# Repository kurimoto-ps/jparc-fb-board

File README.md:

# J-PARC MR 主電磁石電源フィードバック制御子基板

J-PARC メインリング（MR）の主電磁石電源で、電流パタンに沿って電磁石電流を制御するための子基板です。既設のフィードバック母基板 **TEP521C** を使い、その上の **HUMANDATA ACM-205** を、STM32H745 と MAX 10 を搭載した本基板に置き換えます。

既設の光受信、D/A 出力、PLC、変換器盤への Duty 指令は母基板のコネクタを通ります。新たに Ethernet と SDRAM を子基板に持たせ、これまで独立したパタンメモリ基板が担っていた電流指令の受信・保持を取り込むことが設計の狙いです。

光 ADC の混在構成では、MAX 10 が **24 bit × 3 系統**と **16 bit × 8 ch（ADS8568）**を受信します。ACM-205 を置き換えた試作機では、STM32 の起動、SDRAM、Ethernet、FPGA との通信に加え、16 bit 側の全 8 ch のノコギリ波と、24 bit 側の DCCT P/N の一定入力を、それぞれ対応する DAC 出力で確認しました。[ADC の信号経路](docs/interfaces.md) · [実機試験の結果](verification/bench-tests.md)

現行基板では J4 の書き込みケーブルと J5 の RJ45 ジャックに個別の対処を行っています。[既知不具合 3 件と次回改版](docs/errata.md)

```mermaid
flowchart TD
    Host["パタン作成システム"] -->|Ethernet| MCU
    subgraph Board["本基板"]
        MCU["STM32H745"] <-->|FMC 16 bit| RAM["SDRAM 8 MiB"]
        MCU <-->|SPI 4系統| FPGA["MAX 10"]
    end
    Mother["既設フィードバック母基板 TEP521C"]
    MCU <-->|PLC用GPIOなど| Mother
    Mother -->|受信データ・外部同期| FPGA
    FPGA -->|DAC制御・Duty指令など| Mother
    OE["6ch O/E基板"] -->|帰還信号| Mother
    Mother -->|ADS8568 のクロック・変換制御| EO["E/O基板 TEP526A"]
    Mother --> DAC["16ch D/A基板"]
    Mother --> Power["変換器盤への指令"]
```

## 設計を読む

| 知りたいこと | 資料 |
| --- | --- |
| 回路全体と部品の接続 | [回路図 PDF 全6ページ](docs/drawings/schematic.pdf) |
| 基板の配線と両面の部品配置 | [配線・配置図 PDF 全10ページ](docs/drawings/pcb-patterns.pdf) |
| 回路図・PCB の編集 | [KiCad プロジェクト](hardware/kicad/JPARC_PS_FB_BOARD.kicad_pro) |
| プロセッサの役割、電源、メモリ、クロック | [ハードウェア構成](docs/hardware.md) |
| 母基板との対応、ADC/DAC の接点と FPGA ボール | [外部インターフェース](docs/interfaces.md) |
| ランド単位のネット名、部品座標 | [ピン・ネット対応 CSV](hardware/tables/pin-net-mapping.csv) · [部品配置 CSV](hardware/tables/component-locations.csv) |
| 基板製造・部品実装に実際に渡したデータ | [PCBWay の裸基板 Gerber・ドリル、P板.com の実装指示書・部品表・マウントデータ・ステンシル](manufacturing/README.md) |
| 接続・DRC の検査結果と原本の識別 | [設計検証記録](verification/README.md) |

このリポジトリの対象は子基板のハードウェアです。MCU の制御ソフトウェア、MAX 10 の動作用 HDL、閉ループでの追従性能・遅延・ジッタの実測値は収録していません。図は設計上の信号経路を示します。

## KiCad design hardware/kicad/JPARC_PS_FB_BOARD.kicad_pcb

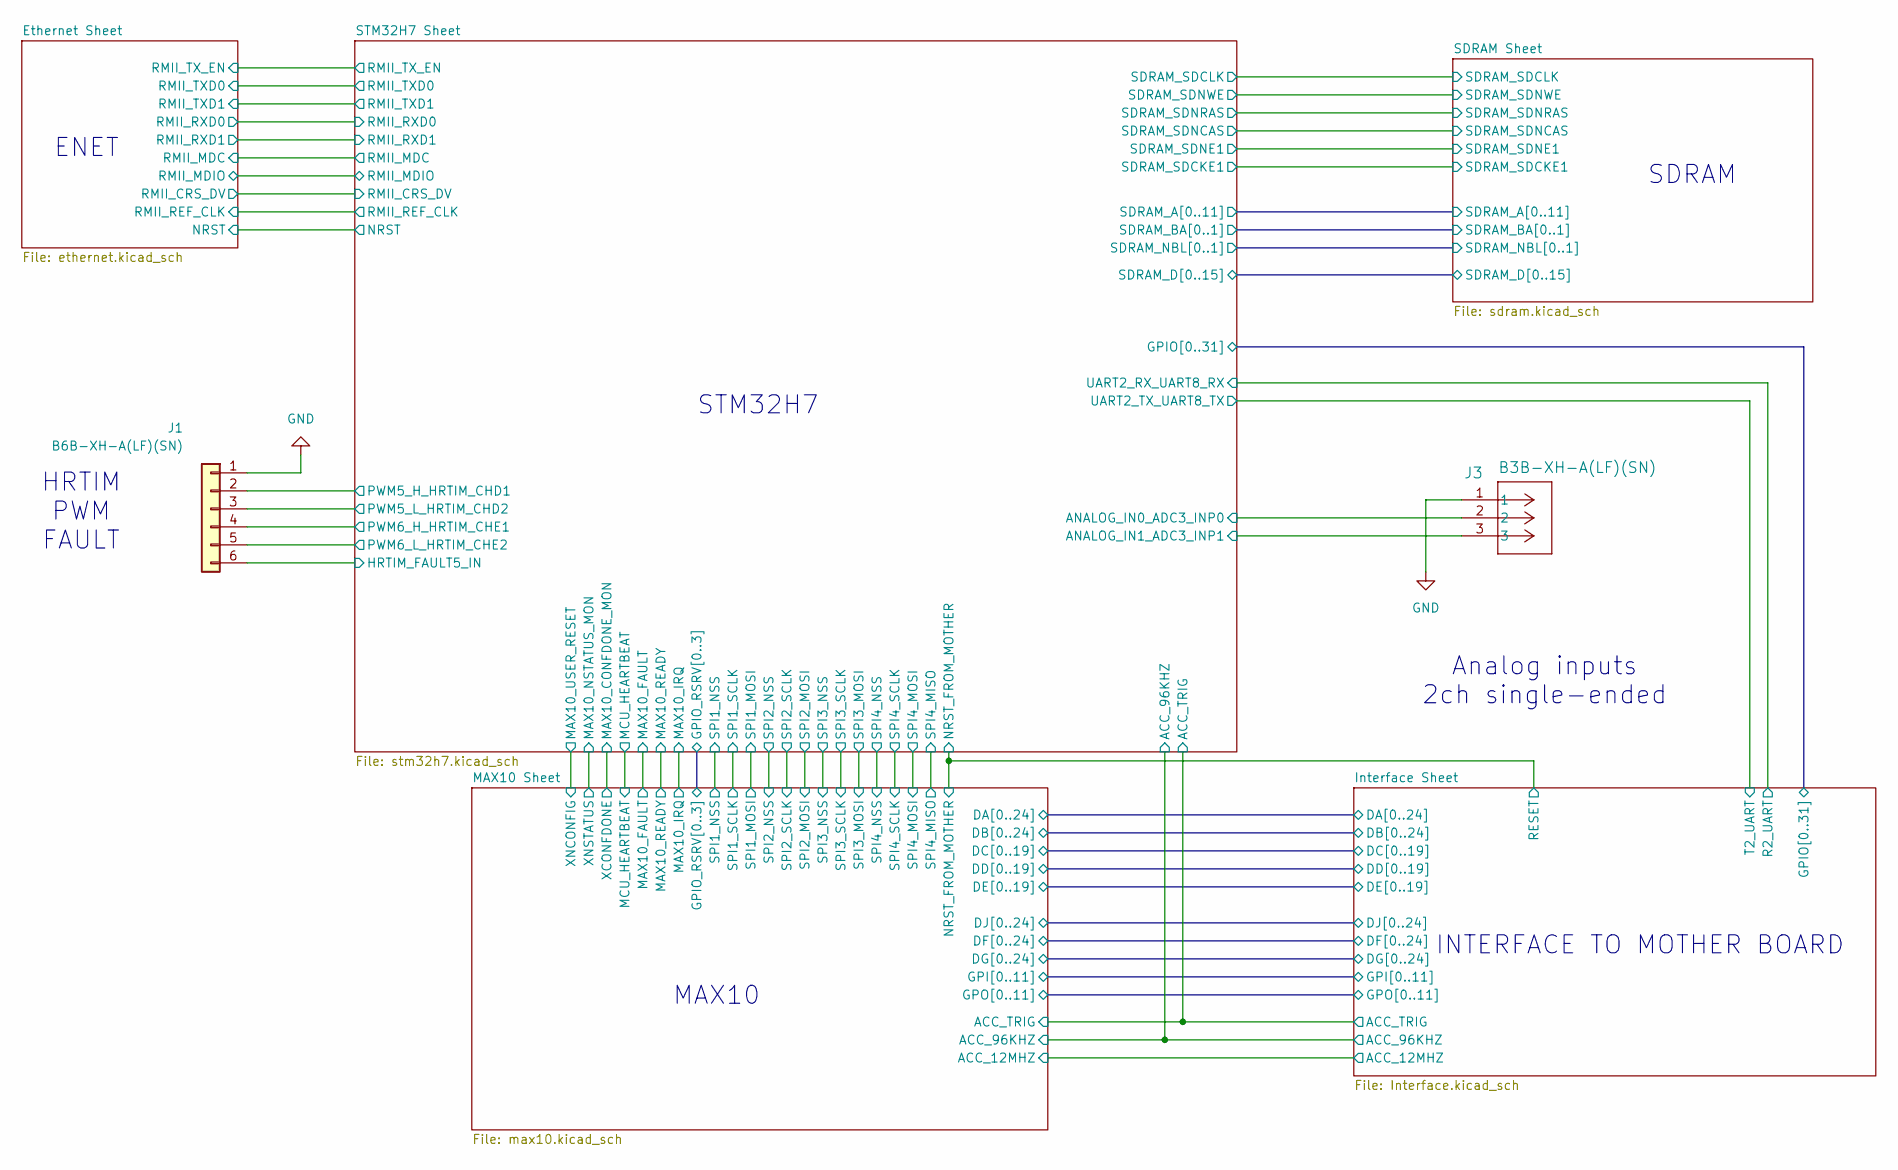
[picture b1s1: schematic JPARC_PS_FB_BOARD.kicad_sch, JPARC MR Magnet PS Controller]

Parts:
J1: B6B-XH-A(LF)(SN); JST_XH_B6B-XH-A_1x06_P2.50mm_Vertical
J3: B3B-XH-A(LF)(SN); JST_XH_B3B-XH-A_1x03_P2.50mm_Vertical

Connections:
/STM32H7 Sheet/PA11: J1.2; also elsewhere on the board
/STM32H7 Sheet/PA12: J1.3; also elsewhere on the board
/STM32H7 Sheet/PC2_C: J3.2; also elsewhere on the board
/STM32H7 Sheet/PC3_C: J3.3; also elsewhere on the board
/STM32H7 Sheet/PG6: J1.4; also elsewhere on the board
/STM32H7 Sheet/PG7: J1.5; also elsewhere on the board
/STM32H7 Sheet/PG10: J1.6; also elsewhere on the board
GND: J1.1, J3.1; also elsewhere on the board

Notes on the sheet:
SDRAM
INTERFACE TO MOTHER BOARD
HRTIM PWM FAULT
Analog inputs 2ch single-ended
MAX10
STM32H7
ENET

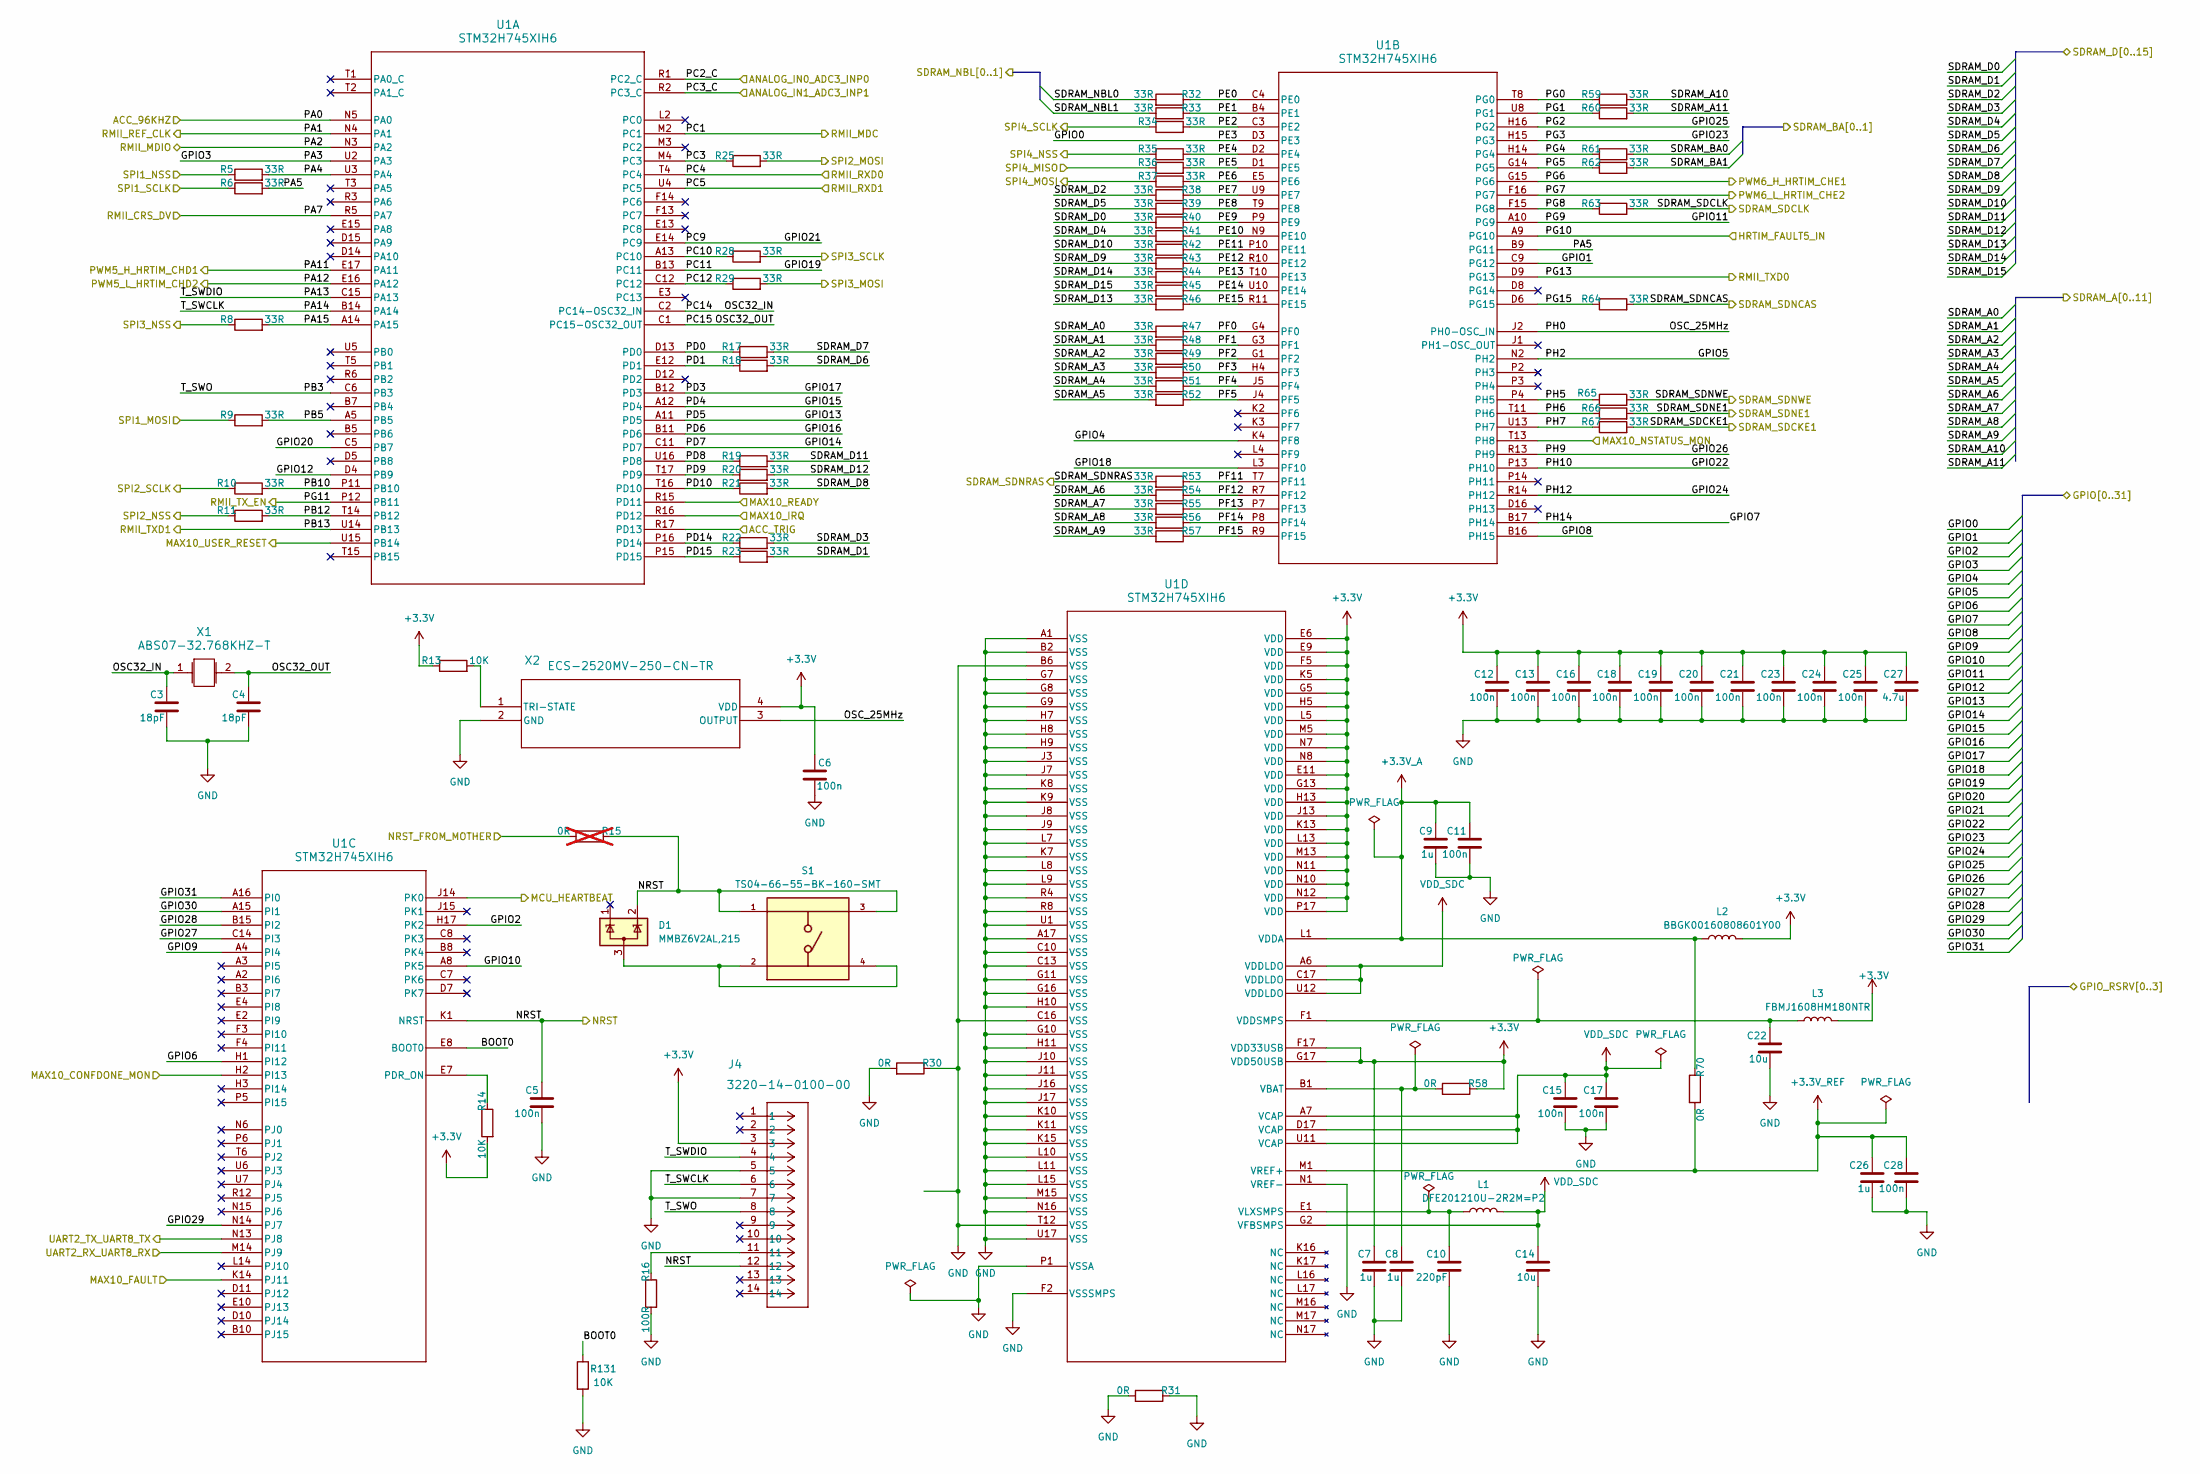
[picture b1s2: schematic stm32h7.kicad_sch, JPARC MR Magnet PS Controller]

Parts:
C3, C4: 18pF; C_0603_1608Metric
C5, C6, C11, C12, C13, C15, C16, C17, C18, C19, C20, C21, C23, C24, C25, C28: 100n; C_0402_1005Metric
C7, C8: 1u; C_0402_1005Metric
C9, C26: 1u; C_0603_1608Metric
C10: 220pF; C_0402_1005Metric
C14, C22: 10u; C_0603_1608Metric
C27: 4.7u; C_0805_2012Metric
D1: MMBZ6V2AL,215; SOT-23-3
J4: 3220-14-0100-00; CNCtech_3220_14_0100_00_Checked
L1: DFE201210U-2R2M=P2; L_Murata_DFE201210U
L2: BBGK00160808601Y00; L_0603_1608Metric
L3: FBMJ1608HM180NTR; L_0603_1608Metric
R5, R6, R8, R9, R10, R11, R17, R18, R19, R20, R21, R22, R23, R25, R28, R29, R32, R33, R34, R35, R36, R37, R38, R39, R40, R41, R42, R43, R44, R45, R46, R47, R48, R49, R50, R51, R52, R53, R54, R55, R56, R57, R59, R60, R61, R62, R63, R64, R65, R66, R67: 33R; R_0402_1005Metric
R13, R14, R131: 10K; R_0603_1608Metric
R15: 0R; R_0603_1608Metric; not fitted
R16: 100R; R_0603_1608Metric
R30, R31, R58, R70: 0R; R_0603_1608Metric
S1: TS04-66-55-BK-160-SMT; SW_TS04-66-55-BK-160-SMT; PARTREV 1.0
U1: STM32H745XIH6; TFBGA240&plus_25
X1: ABS07-32.768KHZ-T; CAP_ABS07-32.768KHZ-T_ABR
X2: ECS-2520MV-250-CN-TR; OSC_ECS-2520MV_ECS

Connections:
+3.3V: C6.1, C7.1, C12.1, C13.1, C16.1, C18.1, C19.1, C20.1, C21.1, C23.1, C24.1, C25.1, C27.1, J4.3, L2.2, L3.1, R13.1, R14.2, R58.1, U1.E6 (VDD), U1.E9 (VDD), U1.E11 (VDD), U1.F5 (VDD), U1.F17 (VDD33USB), U1.G5 (VDD), U1.G13 (VDD), U1.G17 (VDD50USB), U1.H5 (VDD), U1.H13 (VDD), U1.J13 (VDD), U1.K5 (VDD), U1.K13 (VDD), U1.L5 (VDD), U1.L13 (VDD), U1.M5 (VDD), U1.M13 (VDD), U1.N7 (VDD), U1.N8 (VDD), U1.N10 (VDD), U1.N11 (VDD), U1.N12 (VDD), U1.P17 (VDD), X2.4 (VDD); also elsewhere on the board
+3.3V_A: C9.1, C11.1, L2.1, R70.1, U1.L1 (VDDA)
+3.3V_REF: C26.1, C28.1, R70.2, U1.M1 (VREF+)
/Interface Sheet/ACC_TRIG: U1.R17 (PD13); also elsewhere on the board
/Interface Sheet/GPIO0: U1.D3 (PE3); also elsewhere on the board
/Interface Sheet/GPIO1: U1.C9 (PG12); also elsewhere on the board
/Interface Sheet/GPIO2: U1.H17 (PK2); also elsewhere on the board
/Interface Sheet/GPIO3: U1.U2 (PA3); also elsewhere on the board
/Interface Sheet/GPIO4: U1.K4 (PF8); also elsewhere on the board
/Interface Sheet/GPIO5: U1.N2 (PH2); also elsewhere on the board
/Interface Sheet/GPIO6: U1.H1 (PI12); also elsewhere on the board
/Interface Sheet/GPIO7: U1.B17 (PH14); also elsewhere on the board
/Interface Sheet/GPIO8: U1.B16 (PH15); also elsewhere on the board
/Interface Sheet/GPIO9: U1.A4 (PI4); also elsewhere on the board
/Interface Sheet/GPIO10: U1.A8 (PK5); also elsewhere on the board
/Interface Sheet/GPIO11: U1.A10 (PG9); also elsewhere on the board
/Interface Sheet/GPIO12: U1.D4 (PB9); also elsewhere on the board
/Interface Sheet/GPIO13: U1.A11 (PD5); also elsewhere on the board
/Interface Sheet/GPIO14: U1.C11 (PD7); also elsewhere on the board
/Interface Sheet/GPIO15: U1.A12 (PD4); also elsewhere on the board
/Interface Sheet/GPIO16: U1.B11 (PD6); also elsewhere on the board
/Interface Sheet/GPIO17: U1.B12 (PD3); also elsewhere on the board
/Interface Sheet/GPIO18: U1.L3 (PF10); also elsewhere on the board
/Interface Sheet/GPIO19: U1.B13 (PC11); also elsewhere on the board
/Interface Sheet/GPIO20: U1.C5 (PB7); also elsewhere on the board
/Interface Sheet/GPIO21: U1.E14 (PC9); also elsewhere on the board
/Interface Sheet/GPIO22: U1.P13 (PH10); also elsewhere on the board
/Interface Sheet/GPIO23: U1.H15 (PG3); also elsewhere on the board
/Interface Sheet/GPIO24: U1.R14 (PH12); also elsewhere on the board
/Interface Sheet/GPIO25: U1.H16 (PG2); also elsewhere on the board
/Interface Sheet/GPIO26: U1.R13 (PH9); also elsewhere on the board
/Interface Sheet/GPIO27: U1.C14 (PI3); also elsewhere on the board
/Interface Sheet/GPIO28: U1.B15 (PI2); also elsewhere on the board
/Interface Sheet/GPIO29: U1.N14 (PJ7); also elsewhere on the board
/Interface Sheet/GPIO30: U1.A15 (PI1); also elsewhere on the board
/Interface Sheet/GPIO31: U1.A16 (PI0); also elsewhere on the board
/Interface Sheet/R2_UART: U1.M14 (PJ9); also elsewhere on the board
/Interface Sheet/RESET: R15.2; also elsewhere on the board
/Interface Sheet/T2_UART: U1.N13 (PJ8); also elsewhere on the board
/MAX10 Sheet/MAX10_FAULT: U1.K14 (PJ11); also elsewhere on the board
/MAX10 Sheet/MAX10_IRQ: U1.R16 (PD12); also elsewhere on the board
/MAX10 Sheet/MAX10_READY: U1.R15 (PD11); also elsewhere on the board
/MAX10 Sheet/MCU_HEARTBEAT: U1.J14 (PK0); also elsewhere on the board
/MAX10 Sheet/SPI1_MOSI: R9.1; also elsewhere on the board
/MAX10 Sheet/SPI1_NSS: R5.1; also elsewhere on the board
/MAX10 Sheet/SPI1_SCLK: R6.1; also elsewhere on the board
/MAX10 Sheet/SPI2_MOSI: R25.2; also elsewhere on the board
/MAX10 Sheet/SPI2_NSS: R11.1; also elsewhere on the board
/MAX10 Sheet/SPI2_SCLK: R10.1; also elsewhere on the board
/MAX10 Sheet/SPI3_MOSI: R29.2; also elsewhere on the board
/MAX10 Sheet/SPI3_NSS: R8.1; also elsewhere on the board
/MAX10 Sheet/SPI3_SCLK: R28.2; also elsewhere on the board
/MAX10 Sheet/SPI4_MISO: R36.1; also elsewhere on the board
/MAX10 Sheet/SPI4_MOSI: R37.1; also elsewhere on the board
/MAX10 Sheet/SPI4_NSS: R35.1; also elsewhere on the board
/MAX10 Sheet/SPI4_SCLK: R34.1; also elsewhere on the board
/MAX10 Sheet/XCONFDONE: U1.H2 (PI13); also elsewhere on the board
/MAX10 Sheet/XNCONFIG: U1.U15 (PB14); also elsewhere on the board
/MAX10 Sheet/XNSTATUS: U1.T13 (PH8); also elsewhere on the board
/SDRAM Sheet/SDRAM_A0: R47.2; also elsewhere on the board
/SDRAM Sheet/SDRAM_A1: R48.2; also elsewhere on the board
/SDRAM Sheet/SDRAM_A2: R49.2; also elsewhere on the board
/SDRAM Sheet/SDRAM_A3: R50.2; also elsewhere on the board
/SDRAM Sheet/SDRAM_A4: R51.2; also elsewhere on the board
/SDRAM Sheet/SDRAM_A5: R52.2; also elsewhere on the board
/SDRAM Sheet/SDRAM_A6: R54.2; also elsewhere on the board
/SDRAM Sheet/SDRAM_A7: R55.2; also elsewhere on the board
/SDRAM Sheet/SDRAM_A8: R56.2; also elsewhere on the board
/SDRAM Sheet/SDRAM_A9: R57.2; also elsewhere on the board
/SDRAM Sheet/SDRAM_A10: R59.2; also elsewhere on the board
/SDRAM Sheet/SDRAM_A11: R60.2; also elsewhere on the board
/SDRAM Sheet/SDRAM_BA0: R61.2; also elsewhere on the board
/SDRAM Sheet/SDRAM_BA1: R62.2; also elsewhere on the board
/SDRAM Sheet/SDRAM_D0: R40.2; also elsewhere on the board
/SDRAM Sheet/SDRAM_D1: R23.2; also elsewhere on the board
/SDRAM Sheet/SDRAM_D2: R38.2; also elsewhere on the board
/SDRAM Sheet/SDRAM_D3: R22.2; also elsewhere on the board
/SDRAM Sheet/SDRAM_D4: R41.2; also elsewhere on the board
/SDRAM Sheet/SDRAM_D5: R39.2; also elsewhere on the board
/SDRAM Sheet/SDRAM_D6: R18.2; also elsewhere on the board
/SDRAM Sheet/SDRAM_D7: R17.2; also elsewhere on the board
/SDRAM Sheet/SDRAM_D8: R21.2; also elsewhere on the board
/SDRAM Sheet/SDRAM_D9: R43.2; also elsewhere on the board
/SDRAM Sheet/SDRAM_D10: R42.2; also elsewhere on the board
/SDRAM Sheet/SDRAM_D11: R19.2; also elsewhere on the board
/SDRAM Sheet/SDRAM_D12: R20.2; also elsewhere on the board
/SDRAM Sheet/SDRAM_D13: R46.2; also elsewhere on the board
/SDRAM Sheet/SDRAM_D14: R44.2; also elsewhere on the board
/SDRAM Sheet/SDRAM_D15: R45.2; also elsewhere on the board
/SDRAM Sheet/SDRAM_NBL0: R32.2; also elsewhere on the board
/SDRAM Sheet/SDRAM_NBL1: R33.2; also elsewhere on the board
/STM32H7 Sheet/BOOT0: R131.1, U1.E8 (BOOT0)
/STM32H7 Sheet/NRST: C5.1, D1.2 (K), J4.12, R15.1, S1.1, S1.3, U1.K1 (NRST); also elsewhere on the board
/STM32H7 Sheet/OSC32_IN: C3.1, U1.C2 (PC14-OSC32_IN), X1.1
/STM32H7 Sheet/OSC32_OUT: C4.1, U1.C1 (PC15-OSC32_OUT), X1.2
/STM32H7 Sheet/OSC_25MHz: U1.J2 (PH0-OSC_IN), X2.3 (OUTPUT)
/STM32H7 Sheet/PA0: U1.N5 (PA0); also elsewhere on the board
/STM32H7 Sheet/PA1: U1.N4 (PA1); also elsewhere on the board
/STM32H7 Sheet/PA2: U1.N3 (PA2); also elsewhere on the board
/STM32H7 Sheet/PA4: R5.2, U1.U3 (PA4)
/STM32H7 Sheet/PA5: R6.2, U1.B9 (PG11)
/STM32H7 Sheet/PA7: U1.R5 (PA7); also elsewhere on the board
/STM32H7 Sheet/PA11: U1.E17 (PA11); also elsewhere on the board
/STM32H7 Sheet/PA12: U1.E16 (PA12); also elsewhere on the board
/STM32H7 Sheet/PA13: J4.4, U1.C15 (PA13)
/STM32H7 Sheet/PA14: J4.6, U1.B14 (PA14)
/STM32H7 Sheet/PA15: R8.2, U1.A14 (PA15)
/STM32H7 Sheet/PB3: J4.8, U1.C6 (PB3)
/STM32H7 Sheet/PB5: R9.2, U1.A5 (PB5)
/STM32H7 Sheet/PB10: R10.2, U1.P11 (PB10)
/STM32H7 Sheet/PB12: R11.2, U1.T14 (PB12)
/STM32H7 Sheet/PB13: U1.U14 (PB13); also elsewhere on the board
/STM32H7 Sheet/PC1: U1.M2 (PC1); also elsewhere on the board
/STM32H7 Sheet/PC2_C: U1.R1 (PC2_C); also elsewhere on the board
/STM32H7 Sheet/PC3: R25.1, U1.M4 (PC3)
/STM32H7 Sheet/PC3_C: U1.R2 (PC3_C); also elsewhere on the board
/STM32H7 Sheet/PC4: U1.T4 (PC4); also elsewhere on the board
/STM32H7 Sheet/PC5: U1.U4 (PC5); also elsewhere on the board
/STM32H7 Sheet/PC10: R28.1, U1.A13 (PC10)
/STM32H7 Sheet/PC12: R29.1, U1.C12
/STM32H7 Sheet/PD0: R17.1, U1.D13 (PD0)
/STM32H7 Sheet/PD1: R18.1, U1.E12 (PD1)
/STM32H7 Sheet/PD8: R19.1, U1.U16 (PD8)
/STM32H7 Sheet/PD9: R20.1, U1.T17 (PD9)
/STM32H7 Sheet/PD10: R21.1, U1.T16 (PD10)
/STM32H7 Sheet/PD14: R22.1, U1.P16 (PD14)
/STM32H7 Sheet/PD15: R23.1, U1.P15 (PD15)
/STM32H7 Sheet/PE0: R32.1, U1.C4 (PE0)
/STM32H7 Sheet/PE1: R33.1, U1.B4 (PE1)
/STM32H7 Sheet/PE2: R34.2, U1.C3 (PE2)
/STM32H7 Sheet/PE4: R35.2, U1.D2 (PE4)
/STM32H7 Sheet/PE5: R36.2, U1.D1 (PE5)
/STM32H7 Sheet/PE6: R37.2, U1.E5 (PE6)
/STM32H7 Sheet/PE7: R38.1, U1.U9 (PE7)
/STM32H7 Sheet/PE8: R39.1, U1.T9 (PE8)
/STM32H7 Sheet/PE9: R40.1, U1.P9 (PE9)
/STM32H7 Sheet/PE10: R41.1, U1.N9 (PE10)
/STM32H7 Sheet/PE11: R42.1, U1.P10 (PE11)
/STM32H7 Sheet/PE12: R43.1, U1.R10 (PE12)
/STM32H7 Sheet/PE13: R44.1, U1.T10 (PE13)
/STM32H7 Sheet/PE14: R45.1, U1.U10 (PE14)
/STM32H7 Sheet/PE15: R46.1, U1.R11 (PE15)
/STM32H7 Sheet/PF0: R47.1, U1.G4 (PF0)
/STM32H7 Sheet/PF1: R48.1, U1.G3 (PF1)
/STM32H7 Sheet/PF2: R49.1, U1.G1 (PF2)
/STM32H7 Sheet/PF3: R50.1, U1.H4 (PF3)
/STM32H7 Sheet/PF4: R51.1, U1.J5 (PF4)
/STM32H7 Sheet/PF5: R52.1, U1.J4 (PF5)
/STM32H7 Sheet/PF11: R53.1, U1.T7 (PF11)
/STM32H7 Sheet/PF12: R54.1, U1.R7 (PF12)
/STM32H7 Sheet/PF13: R55.1, U1.P7 (PF13)
/STM32H7 Sheet/PF14: R56.1, U1.P8 (PF14)
/STM32H7 Sheet/PF15: R57.1, U1.R9 (PF15)
/STM32H7 Sheet/PG0: R59.1, U1.T8 (PG0)
/STM32H7 Sheet/PG1: R60.1, U1.U8 (PG1)
/STM32H7 Sheet/PG4: R61.1, U1.H14 (PG4)
/STM32H7 Sheet/PG5: R62.1, U1.G14 (PG5)
/STM32H7 Sheet/PG6: U1.G15 (PG6); also elsewhere on the board
/STM32H7 Sheet/PG7: U1.F16 (PG7); also elsewhere on the board
/STM32H7 Sheet/PG8: R63.1, U1.F15 (PG8)
/STM32H7 Sheet/PG10: U1.A9 (PG10); also elsewhere on the board
/STM32H7 Sheet/PG11: U1.P12 (PB11); also elsewhere on the board
/STM32H7 Sheet/PG13: U1.D9 (PG13); also elsewhere on the board
/STM32H7 Sheet/PG15: R64.1, U1.D6 (PG15)
/STM32H7 Sheet/PH5: R65.1, U1.P4 (PH5)
/STM32H7 Sheet/PH6: R66.1, U1.T11 (PH6)
/STM32H7 Sheet/PH7: R67.1, U1.U13 (PH7)
/STM32H7 Sheet/SDRAM_SDCKE1: R67.2; also elsewhere on the board
/STM32H7 Sheet/SDRAM_SDCLK: R63.2; also elsewhere on the board
/STM32H7 Sheet/SDRAM_SDNCAS: R64.2; also elsewhere on the board
/STM32H7 Sheet/SDRAM_SDNE1: R66.2; also elsewhere on the board
/STM32H7 Sheet/SDRAM_SDNRAS: R53.2; also elsewhere on the board
/STM32H7 Sheet/SDRAM_SDNWE: R65.2; also elsewhere on the board
GND: C3.2, C4.2, C5.2, C6.2, C7.2, C8.2, C9.2, C10.2, C11.2, C12.2, C13.2, C14.2, C15.2, C16.2, C17.2, C18.2, C19.2, C20.2, C21.2, C22.2, C23.2, C24.2, C25.2, C26.2, C27.2, C28.2, J4.5, J4.7, R16.2, R30.1, R30.2, R31.1, R31.2, R131.2, U1.A1 (VSS), U1.A17 (VSS), U1.B2 (VSS), U1.B6 (VSS), U1.C10 (VSS), U1.C13 (VSS), U1.C16 (VSS), U1.F2 (VSSSMPS), U1.G7 (VSS), U1.G8 (VSS), U1.G9 (VSS), U1.G10 (VSS), U1.G11 (VSS), U1.G16 (VSS), U1.H7 (VSS), U1.H8 (VSS), U1.H9 (VSS), U1.H10 (VSS), U1.H11 (VSS), U1.J3 (VSS), U1.J7 (VSS), U1.J8 (VSS), U1.J9 (VSS), U1.J10 (VSS), U1.J11 (VSS), U1.J16 (VSS), U1.J17 (VSS), U1.K7 (VSS), U1.K8 (VSS), U1.K9 (VSS), U1.K10 (VSS), U1.K11 (VSS), U1.K15 (VSS), U1.L7 (VSS), U1.L8 (VSS), U1.L9 (VSS), U1.L10 (VSS), U1.L11 (VSS), U1.L15 (VSS), U1.M15 (VSS), U1.N1 (VREF-), U1.N16 (VSS), U1.P1 (VSSA), U1.R4 (VSS), U1.R8 (VSS), U1.T12 (VSS), U1.U1 (VSS), U1.U17 (VSS), X2.2 (GND); also elsewhere on the board
unnamed: D1.3 (A), S1.2, S1.4
unnamed: J4.11, R16.1
unnamed: R14.1, U1.E7 (PDR_ON)
unnamed: C8.1, R58.2, U1.B1 (VBAT)
unnamed: C22.1, L3.2, U1.F1 (VDDSMPS)
unnamed: C10.1, L1.2, U1.E1 (VLXSMPS)
unnamed: R13.2, X2.1 (TRI-STATE)
VDD_SDC: C14.1, C15.1, C17.1, L1.1, U1.A6 (VDDLDO), U1.A7 (VCAP), U1.C17 (VDDLDO), U1.D17 (VCAP), U1.G2 (VFBSMPS), U1.U11 (VCAP), U1.U12 (VDDLDO)

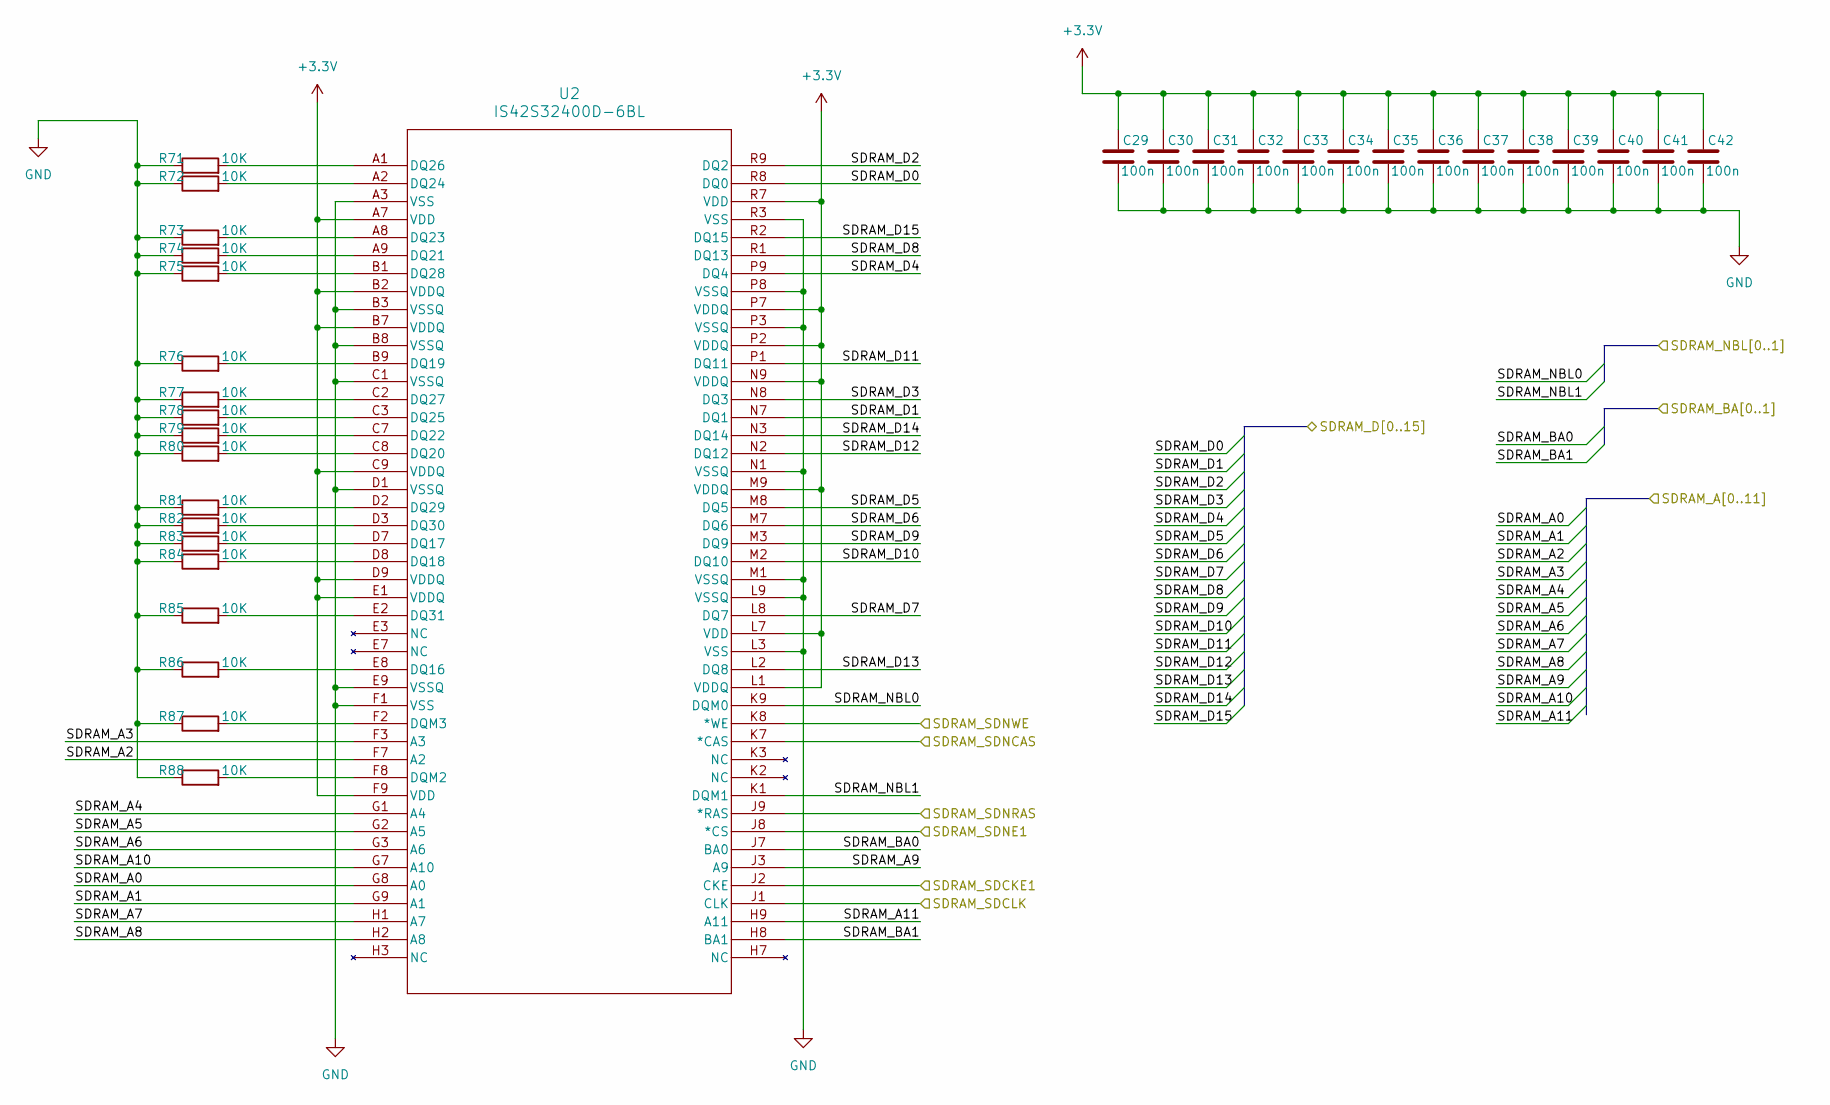
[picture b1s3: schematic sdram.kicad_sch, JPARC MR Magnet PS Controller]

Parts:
C29, C30, C31, C32, C33, C34, C35, C36, C37, C38, C39, C40, C41, C42: 100n; C_0402_1005Metric
R71, R72, R73, R74, R75, R76, R77, R78, R79, R80, R81, R82, R83, R84, R85, R86, R87, R88: 10K; R_0603_1608Metric
U2: IS42S32400D-6BL; TFBGA-90_8X13_ISI

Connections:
+3.3V: C29.1, C30.1, C31.1, C32.1, C33.1, C34.1, C35.1, C36.1, C37.1, C38.1, C39.1, C40.1, C41.1, C42.1, U2.A7 (VDD), U2.B2 (VDDQ), U2.B7 (VDDQ), U2.C9 (VDDQ), U2.D9 (VDDQ), U2.E1 (VDDQ), U2.F9 (VDD), U2.L1 (VDDQ), U2.L7 (VDD), U2.M9 (VDDQ), U2.N9 (VDDQ), U2.P2 (VDDQ), U2.P7 (VDDQ), U2.R7 (VDD); also elsewhere on the board
/SDRAM Sheet/SDRAM_A0: U2.G8 (A0); also elsewhere on the board
/SDRAM Sheet/SDRAM_A1: U2.G9 (A1); also elsewhere on the board
/SDRAM Sheet/SDRAM_A2: U2.F7 (A2); also elsewhere on the board
/SDRAM Sheet/SDRAM_A3: U2.F3 (A3); also elsewhere on the board
/SDRAM Sheet/SDRAM_A4: U2.G1 (A4); also elsewhere on the board
/SDRAM Sheet/SDRAM_A5: U2.G2 (A5); also elsewhere on the board
/SDRAM Sheet/SDRAM_A6: U2.G3 (A6); also elsewhere on the board
/SDRAM Sheet/SDRAM_A7: U2.H1 (A7); also elsewhere on the board
/SDRAM Sheet/SDRAM_A8: U2.H2 (A8); also elsewhere on the board
/SDRAM Sheet/SDRAM_A9: U2.J3 (A9); also elsewhere on the board
/SDRAM Sheet/SDRAM_A10: U2.G7 (A10); also elsewhere on the board
/SDRAM Sheet/SDRAM_A11: U2.H9 (A11); also elsewhere on the board
/SDRAM Sheet/SDRAM_BA0: U2.J7 (BA0); also elsewhere on the board
/SDRAM Sheet/SDRAM_BA1: U2.H8 (BA1); also elsewhere on the board
/SDRAM Sheet/SDRAM_D0: U2.R8 (DQ0); also elsewhere on the board
/SDRAM Sheet/SDRAM_D1: U2.N7 (DQ1); also elsewhere on the board
/SDRAM Sheet/SDRAM_D2: U2.R9 (DQ2); also elsewhere on the board
/SDRAM Sheet/SDRAM_D3: U2.N8 (DQ3); also elsewhere on the board
/SDRAM Sheet/SDRAM_D4: U2.P9 (DQ4); also elsewhere on the board
/SDRAM Sheet/SDRAM_D5: U2.M8 (DQ5); also elsewhere on the board
/SDRAM Sheet/SDRAM_D6: U2.M7 (DQ6); also elsewhere on the board
/SDRAM Sheet/SDRAM_D7: U2.L8 (DQ7); also elsewhere on the board
/SDRAM Sheet/SDRAM_D8: U2.R1 (DQ13); also elsewhere on the board
/SDRAM Sheet/SDRAM_D9: U2.M3 (DQ9); also elsewhere on the board
/SDRAM Sheet/SDRAM_D10: U2.M2 (DQ10); also elsewhere on the board
/SDRAM Sheet/SDRAM_D11: U2.P1 (DQ11); also elsewhere on the board
/SDRAM Sheet/SDRAM_D12: U2.N2 (DQ12); also elsewhere on the board
/SDRAM Sheet/SDRAM_D13: U2.L2 (DQ8); also elsewhere on the board
/SDRAM Sheet/SDRAM_D14: U2.N3 (DQ14); also elsewhere on the board
/SDRAM Sheet/SDRAM_D15: U2.R2 (DQ15); also elsewhere on the board
/SDRAM Sheet/SDRAM_NBL0: U2.K9 (DQM0); also elsewhere on the board
/SDRAM Sheet/SDRAM_NBL1: U2.K1 (DQM1); also elsewhere on the board
/STM32H7 Sheet/SDRAM_SDCKE1: U2.J2 (CKE); also elsewhere on the board
/STM32H7 Sheet/SDRAM_SDCLK: U2.J1 (CLK); also elsewhere on the board
/STM32H7 Sheet/SDRAM_SDNCAS: U2.K7 (*CAS); also elsewhere on the board
/STM32H7 Sheet/SDRAM_SDNE1: U2.J8 (*CS); also elsewhere on the board
/STM32H7 Sheet/SDRAM_SDNRAS: U2.J9 (*RAS); also elsewhere on the board
/STM32H7 Sheet/SDRAM_SDNWE: U2.K8 (*WE); also elsewhere on the board
GND: C29.2, C30.2, C31.2, C32.2, C33.2, C34.2, C35.2, C36.2, C37.2, C38.2, C39.2, C40.2, C41.2, C42.2, R71.1, R72.1, R73.1, R74.1, R75.1, R76.1, R77.1, R78.1, R79.1, R80.1, R81.1, R82.1, R83.1, R84.1, R85.1, R86.1, R87.1, R88.1, U2.A3 (VSS), U2.B3 (VSSQ), U2.B8 (VSSQ), U2.C1 (VSSQ), U2.D1 (VSSQ), U2.E9 (VSSQ), U2.F1 (VSS), U2.L3 (VSS), U2.L9 (VSSQ), U2.M1 (VSSQ), U2.N1 (VSSQ), U2.P3 (VSSQ), U2.P8 (VSSQ), U2.R3 (VSS); also elsewhere on the board
unnamed: R86.2, U2.E8 (DQ16)
unnamed: R83.2, U2.D7 (DQ17)
unnamed: R84.2, U2.D8 (DQ18)
unnamed: R76.2, U2.B9 (DQ19)
unnamed: R80.2, U2.C8 (DQ20)
unnamed: R74.2, U2.A9 (DQ21)
unnamed: R79.2, U2.C7 (DQ22)
unnamed: R73.2, U2.A8 (DQ23)
unnamed: R72.2, U2.A2 (DQ24)
unnamed: R78.2, U2.C3 (DQ25)
unnamed: R71.2, U2.A1 (DQ26)
unnamed: R77.2, U2.C2 (DQ27)
unnamed: R75.2, U2.B1 (DQ28)
unnamed: R81.2, U2.D2 (DQ29)
unnamed: R82.2, U2.D3 (DQ30)
unnamed: R85.2, U2.E2 (DQ31)
unnamed: R88.2, U2.F8 (DQM2)
unnamed: R87.2, U2.F2 (DQM3)
